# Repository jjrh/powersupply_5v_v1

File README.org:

* dual rail 5v regulated powersupply
  The main target is the [[http://github.com/jjrh/PGA2311][PGA2311]] however other devices
  should work subsituting the LM7805 & LM7905 with appropiate
  parts

  #+CAPTION: 2015-11-05 schematic
  #+NAME:   fig:0
  #+attr_html: :width 800px
  [[./images/powersupply_5v_v1.sch.png]]

  #+CAPTION: 2015-11-05 3d pcb layout
  #+NAME:   fig:0
  #+attr_html: :width 800px
  [[./images/powersupply_5v_v1_3d1.png]]

  based on:
      http://elinux.org/RPi_5V_PSU_construction

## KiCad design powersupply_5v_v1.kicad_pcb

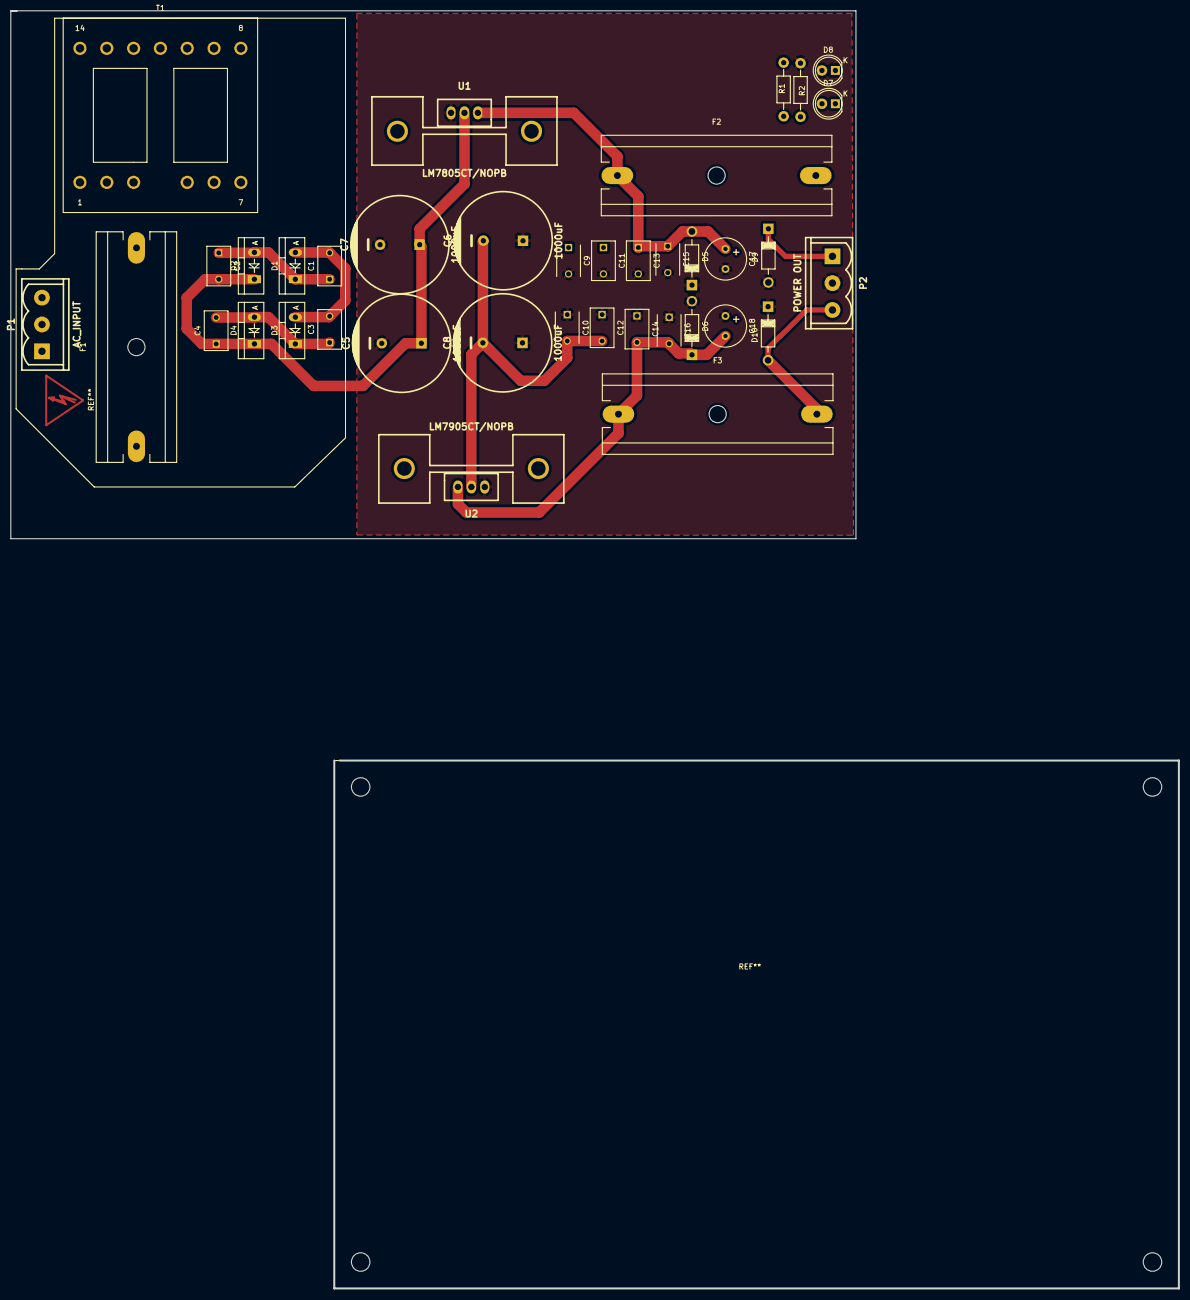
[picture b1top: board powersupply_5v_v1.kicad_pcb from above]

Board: 2 copper layers, 160.1 x 100.0 mm, 38 parts (0 on the bottom side), 14 nets.

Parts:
C1, C2, C3, C4: C_Small; C_Disc_D7.5_P5
C5, C6, C7, C8: 1000uF; CP_18x16mm
C9, C10, C15, C16: 10nF; C_Disc_D6_P5
C11, C12, C13, C14: 100nF; C_Disc_D7.5_P5
C17, C18: 470uF; Elko_vert_11.5x8mm_RM3.5
D1, D2, D3, D4: MUR860G; Diode_TO-220_Vertical
D5, D6: TVS; Diode_DO-41_SOD81_Horizontal_RM10
D7, D8: LED; LED-5MM
D9, D10: 1N4008; Diode_DO-41_SOD81_Horizontal_RM10
F1, F2, F3: FUSE; Fuseholder6x32_Horiz_Open_Schurter0031-8002
P1: AC_INPUT; mstbva_2,5%2f3-g-5,08
P2: POWER OUT; mstbva_2,5%2f3-g-5,08
R1: R; Resistor_Horizontal_RM10mm
R2: R_Small; Resistor_Horizontal_RM10mm
T1: TRANSFO2; ETD29_13Pin_Horizontal_EPCOS-B66359A1013T
U1: LM7805CT/NOPB; to220_std_14cw
U2: LM7905CT/NOPB; to220_std_14cw

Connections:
/HOT: F1.1, P1.1
/NETURAL: P1.2, T1.2
/REG_+5V: D9.1, F2.2, P2.1
/REG_-5V: D10.2, F3.2, P2.3
/V+: C2.2, C4.1, C5.1, C7.1, C9.1, C11.1, D2.1, D4.1, U1.2
/V-: C1.2, C3.2, C6.2, C8.2, C10.2, C12.2, D1.2, D3.2, U2.2
GNDPWR: C5.2, C6.1, C7.2, C8.1, C9.2, C10.1, C11.2, C12.1, C13.2, C14.1, C15.2, C16.1, C17.2, C18.1, D5.1, D6.2, D8.2, D9.2, D10.1, P2.2, R1.2, T1.5, U1.1, U2.1
unnamed: C1.1, C2.1, D1.1, D2.2, T1.3
unnamed: C3.1, C4.2, D3.1, D4.2, T1.6
unnamed: C13.1, C15.1, C17.1, D5.2, D7.2, F2.1, U1.3
unnamed: C14.2, C16.2, C18.2, D6.1, F3.1, R2.2, U2.3
unnamed: D7.1, R1.1
unnamed: D8.1, R2.1
unnamed: F1.2, T1.1

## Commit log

2015-08-29 initialized repo
2015-08-29 link to the pga2311 project
2015-08-29 https links don't work?
2015-08-29 typo
2015-10-23 initialized
2015-10-23 annoated schematic and added labels
2015-11-04 bunch of stuff wasn't commited...
2015-11-05 added footprint that was screwed up
2015-11-05 various pcb changes
2015-11-06 added some symbol stuff
2015-11-06 trying to get this hammond transformer footprint made
2015-11-06 added some PDF's for the hammond transformer
2015-11-06 added exported image of 2015-11-05 schematic
2015-11-06 added 3d image
2015-11-07 added a small circuit for showing a LED indication when AC power is live
